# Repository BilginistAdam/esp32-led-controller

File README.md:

<p align="center">
  <picture>
    <source media="(prefers-color-scheme: dark)" srcset="docs/logo/banner-dark.svg">
    
  </picture>
</p>

# LED Controller — ESP32-C3 LED Şerit Kontrolcüsü

12–24 V LED şeritleri WiFi üzerinden açıp kapatan ve PWM ile dimleyen küçük bir kontrol kartı. Proje KiCad donanım dosyalarını, iki firmware seçeneğini (ESPHome / PlatformIO) ve 3D yazıcıyla basılabilen bir kutuyu içerir.

| PCB üst | Şematik |
|---|---|
|  |  |

## Özellikler

- **Kontrol:** ESP32-C3-WROOM-02 (WiFi + BLE). Programlama dahili USB üzerinden USB-C ile yapılıyor, ayrı bir USB-UART çipi yok.
- **Giriş:** 12–24 V DC. PTC sigorta ve TVS ile korunuyor. AP63203 buck regülatör 3.3 V üretiyor.
- **Besleme:** D1/D2 diyotlarıyla kart adaptörden **ya da** sadece USB'den beslenebiliyor, yani programlarken adaptör gerekmiyor.
- **LED sürme:** LED şeridini low-side AO3400A MOSFET anahtarlıyor. 20 kHz PWM kullanılıyor, böylece duyulabilir vızıltı olmuyor. Gate'teki pull-down sayesinde LED boot sırasında kapalı kalıyor.
- **Arayüz:** RESET butonu, BOOT/kullanıcı butonu ve durum LED'i var.
- **Kart:** 64 × 38 mm, 2 katman, 4 × M3 montaj deliği.

## Klasör yapısı

```
hardware/          KiCad projesi (şematik, PCB, proje sembol kütüphanesi)
  BOM.md / BOM.csv malzeme listesi (okunabilir tablo / üretici formatı)
  ledctl-gerbers.zip   üreticiye (JLCPCB/PCBWay vb.) doğrudan yüklenebilir
  fabrication/     Gerber, drill, pick-and-place (pos) dosyaları
  scripts/         şematik/PCB'yi üreten Python betikleri (design.py = tek kaynak)
firmware/
  esphome/         Home Assistant için ESPHome konfigürasyonu
  platformio/      bağımsız Arduino firmware'i (web arayüzü + REST API)
    prebuilt/      derlenmiş factory imajı (0x0 adresine yazılır)
enclosure/         OpenSCAD kaynak + basılmaya hazır STL'ler
docs/              şematik PDF, PCB montaj PDF'i, görseller
  logo/            Bilginier logosu (SVG) + üretici betik (PCB, kutu ve banner aynı kaynaktan)
```

## Malzeme listesi (BOM)

Ayrıntılı liste için [`hardware/BOM.md`](hardware/BOM.md), makineli montaj için [`hardware/BOM.csv`](hardware/BOM.csv) dosyasına bak.

| Adet | Ref | Parça | LCSC |
|---:|---|---|---|
| 1 | U2 | ESP32-C3-WROOM-02-N4 | C2934560 |
| 1 | U1 | AP63203WU-7 (3.3 V buck) | C780769 |
| 1 | Q1 | AO3400A | C20917 |
| 1 | L1 | FNR4030S4R7MT, 4.7 µH | C167874 |
| 1 / 1 / 1 | D1 / D2 / D3 | SS34 / SS14 / SMAJ28A | C8678 / C2480 / C353458 |
| 1 | D4 | Yeşil LED 0603 | C72043 |
| 1 | F1 | PTC 1812 (bkz. BOM.md notu) | — |
| 1 | C1 | 10 µF 50 V 1206 | C13585 |
| 3 | C2, C3, C7 | 100 nF 50 V 0603 | C14663 |
| 2 | C4, C5 | 22 µF 25 V 0805 | C45783 |
| 1 / 1 | C6 / C8 | 10 µF 0805 / 1 µF 0603 | C15850 / C15849 |
| 4 | R1–R4 | 10 kΩ 0603 | C25804 |
| 1 / 1 / 1 | R5 / R6 / R7 | 100 Ω / 100 kΩ / 1 kΩ 0603 | C22775 / C25803 / C21190 |
| 2 | R8, R9 | 5.1 kΩ 0603 | C23186 |
| 2 | J1, J2 | Phoenix 1715721, 2P 5.08 mm | C480516 |
| 1 | J3 | USB-C HRO TYPE-C-31-M-12 | C165948 |
| 1 | J4 | 1×4 pin header (opsiyonel) | C2337 |
| 2 | SW1, SW2 | TS-1187A-B-A-B | C318884 |
| 4 | — | M3 × 20 vida (kutu) | — |

JLCPCB montaj için hazır dosyalar: `hardware/fabrication/ledctl-bom-jlcpcb.csv` ve `ledctl-cpl-jlcpcb.csv`.

## Pin haritası

| GPIO | İşlev |
|---|---|
| IO4 | LED PWM → R5 → Q1 gate |
| IO9 | BOOT / kullanıcı butonu (aktif düşük) |
| IO10 | Durum LED'i (aktif yüksek) |
| IO18 / IO19 | USB D− / D+ (USB-C) |
| IO20 / IO21 | UART RX / TX (J4, opsiyonel) |

## Firmware

### Seçenek A: ESPHome (Home Assistant)

```bash
cd firmware/esphome
cp secrets.yaml.example secrets.yaml   # WiFi bilgilerini gir
esphome run ledctl.yaml                # ilk yükleme USB-C üzerinden
```

Bu seçenek Home Assistant'a "LED Serit" adlı, dimlenebilir bir ışık olarak eklenir. Butona basınca LED açılıp kapanır, durum LED'i WiFi bağlantısını gösterir.

### Seçenek B: PlatformIO (bağımsız)

```bash
cd firmware/platformio
pio run -t upload        # USB-C
pio device monitor
```

1. **WiFi kurulumu:** İlk açılışta kart `LedCtrl-Setup` adında bir WiFi ağı açar. Bu ağa bağlanıp açılan sayfadan kendi WiFi bilgilerini gir.
2. **Web arayüzü:** Kurulumdan sonra `http://led-ctrl.local` adresinden aç/kapat ve parlaklık ayarı yapılabilir.
3. **REST API:**
   ```bash
   curl http://led-ctrl.local/api/state
   curl -X POST http://led-ctrl.local/api/state -d '{"on":true,"brightness":60}'
   curl -X POST http://led-ctrl.local/api/toggle
   ```
4. **Buton:**
   - Kısa basış: aç/kapat
   - Basılı tutma: parlaklığı 100 → 75 → 50 → 25 → 10 sırasıyla değiştirir
   - 8 saniye basılı tutma: WiFi ayarlarını siler
5. **Durum LED'i:**
   - Sürekli yanık: bağlı
   - Yavaş yanıp sönme: bağlanıyor
   - Hızlı yanıp sönme: kurulum modunda
6. **Diğer:** Son durum NVS'e kaydedilir, elektrik kesilip gelince geri yüklenir. Ayrıca OTA güncelleme (ArduinoOTA) destekleniyor.

Hazır imajı yazmak için:

```bash
esptool.py --chip esp32c3 write_flash 0x0 firmware/platformio/prebuilt/ledctl-factory.bin
```

> **Yükleme başlamazsa:** **BOOT**'a basılı tutarken **RESET**'e bas ve bırak. Kart indirme moduna geçer. Normalde USB üzerinden otomatik reset yeterli olur.

## Kutu (3D baskı)

| Parça | Dosya | Baskı yönü |
|---|---|---|
| Gövde | `enclosure/ledctl_case_base.stl` | taban aşağıda |
| Kapak | `enclosure/ledctl_case_lid.stl` | yüzü aşağıda (dosya zaten bu yönde) |

- **Önerilen baskı ayarları:** PETG veya PLA, 0.2 mm katman, %20–30 doluluk. Destek gerekmiyor.
- **Montaj:** 4 adet **M3 × 20** vida kapaktan girer, PCB'yi sıkıştırır ve gövdedeki direklere tutunur. Vidalar plastiğe kendi yolunu açabilir; isteğe bağlı olarak `pilot_d = 4.0` ile heat-set insert de kullanılabilir.
- **Duvara montaj:** Tabanda 20 mm aralıklı iki anahtar deliği var, en fazla 8 mm başlı vida uygun. USB-C aşağı bakacak şekilde asılır.
- **Bantla montaj:** Taban tamamen düz olduğu için çift taraflı bantla da yapıştırılabilir.
- **Butonlar:** RESET ve BOOT butonları kapaktaki esnek dillerle basılır. Durum LED'inin ışığı kapaktaki tüpten görünür.
- **Terminaller:** Vidalarına kapaktaki deliklerden tornavidayla erişilir.
- **Ölçüler:** `enclosure/ledctl_case.scad` içindeki parametrelerden (tolerans, duvar kalınlığı, yükseklik) değiştirilebilir.

```bash
openscad -D 'part="base"' -o enclosure/ledctl_case_base.stl enclosure/ledctl_case.scad
openscad -D 'part="lid"'  -o enclosure/ledctl_case_lid.stl  enclosure/ledctl_case.scad
```

## Üretim

1. `hardware/ledctl-gerbers.zip` dosyasını PCB üreticisine yükle. Ayarlar: 2 katman, 1.6 mm, 1 oz bakır.
2. Montaj için `hardware/BOM.csv` (okunabilir hali: `hardware/BOM.md`) ve `hardware/fabrication/ledctl-pos.csv` dosyalarını kullan.
3. ESP modülünün anteni kartın sağ kenarından yaklaşık 6 mm dışarı taşar. Bu bilinçli bir tercih: antenin altında bakır olmaması gerekiyor. Kutu bu taşmaya göre tasarlandı.

## Tasarım notları ve sınırlar

- **Akım:** AO3400A ile kart yaklaşık **3 A** LED akımı için uygun. 24 V'ta bu yaklaşık 70 W, 12 V'ta yaklaşık 36 W eder. Daha yüksek akım için daha güçlü bir MOSFET kullanılmalı ve LED izleri genişletilmeli.
- **Gerilim:** AP63203 en fazla 32 V girişe dayanır. 24 V adaptörlerde sorun yok. TVS (SMAJ28A) kısa süreli darbelere karşı korur, ama sürekli aşırı gerilimden korumaz.
- **F1 sigorta:** 3 A / 24 V için 1812 kılıfta uygun bir PTC yok. Seçenekler [`hardware/BOM.md`](hardware/BOM.md) notunda anlatılıyor.
- **Routing:** İzler Freerouting ile otomatik çizildi. DRC'de elektriksel hata yok, sadece kozmetik silkscreen uyarıları var. Sipariş vermeden önce KiCad 8/9'da ERC ve DRC'yi kendin de çalıştır.
- **Yeniden üretme:** `hardware/scripts/` içindeki betikler şematik ve PCB'yi `design.py` ve `placement.py` dosyalarından üretir. Logo ve isim en son `add_branding.py` ile silkscreen'e eklenir. Bunun için KiCad 7+ Python (`pcbnew`) ve otomatik routing için Freerouting gerekir (`FREEROUTING_JAR` ortam değişkeni).

## Lisans

[MIT](LICENSE). Donanım dosyaları, firmware ve kutu dahil projenin tamamı bu lisansla yayınlanır.

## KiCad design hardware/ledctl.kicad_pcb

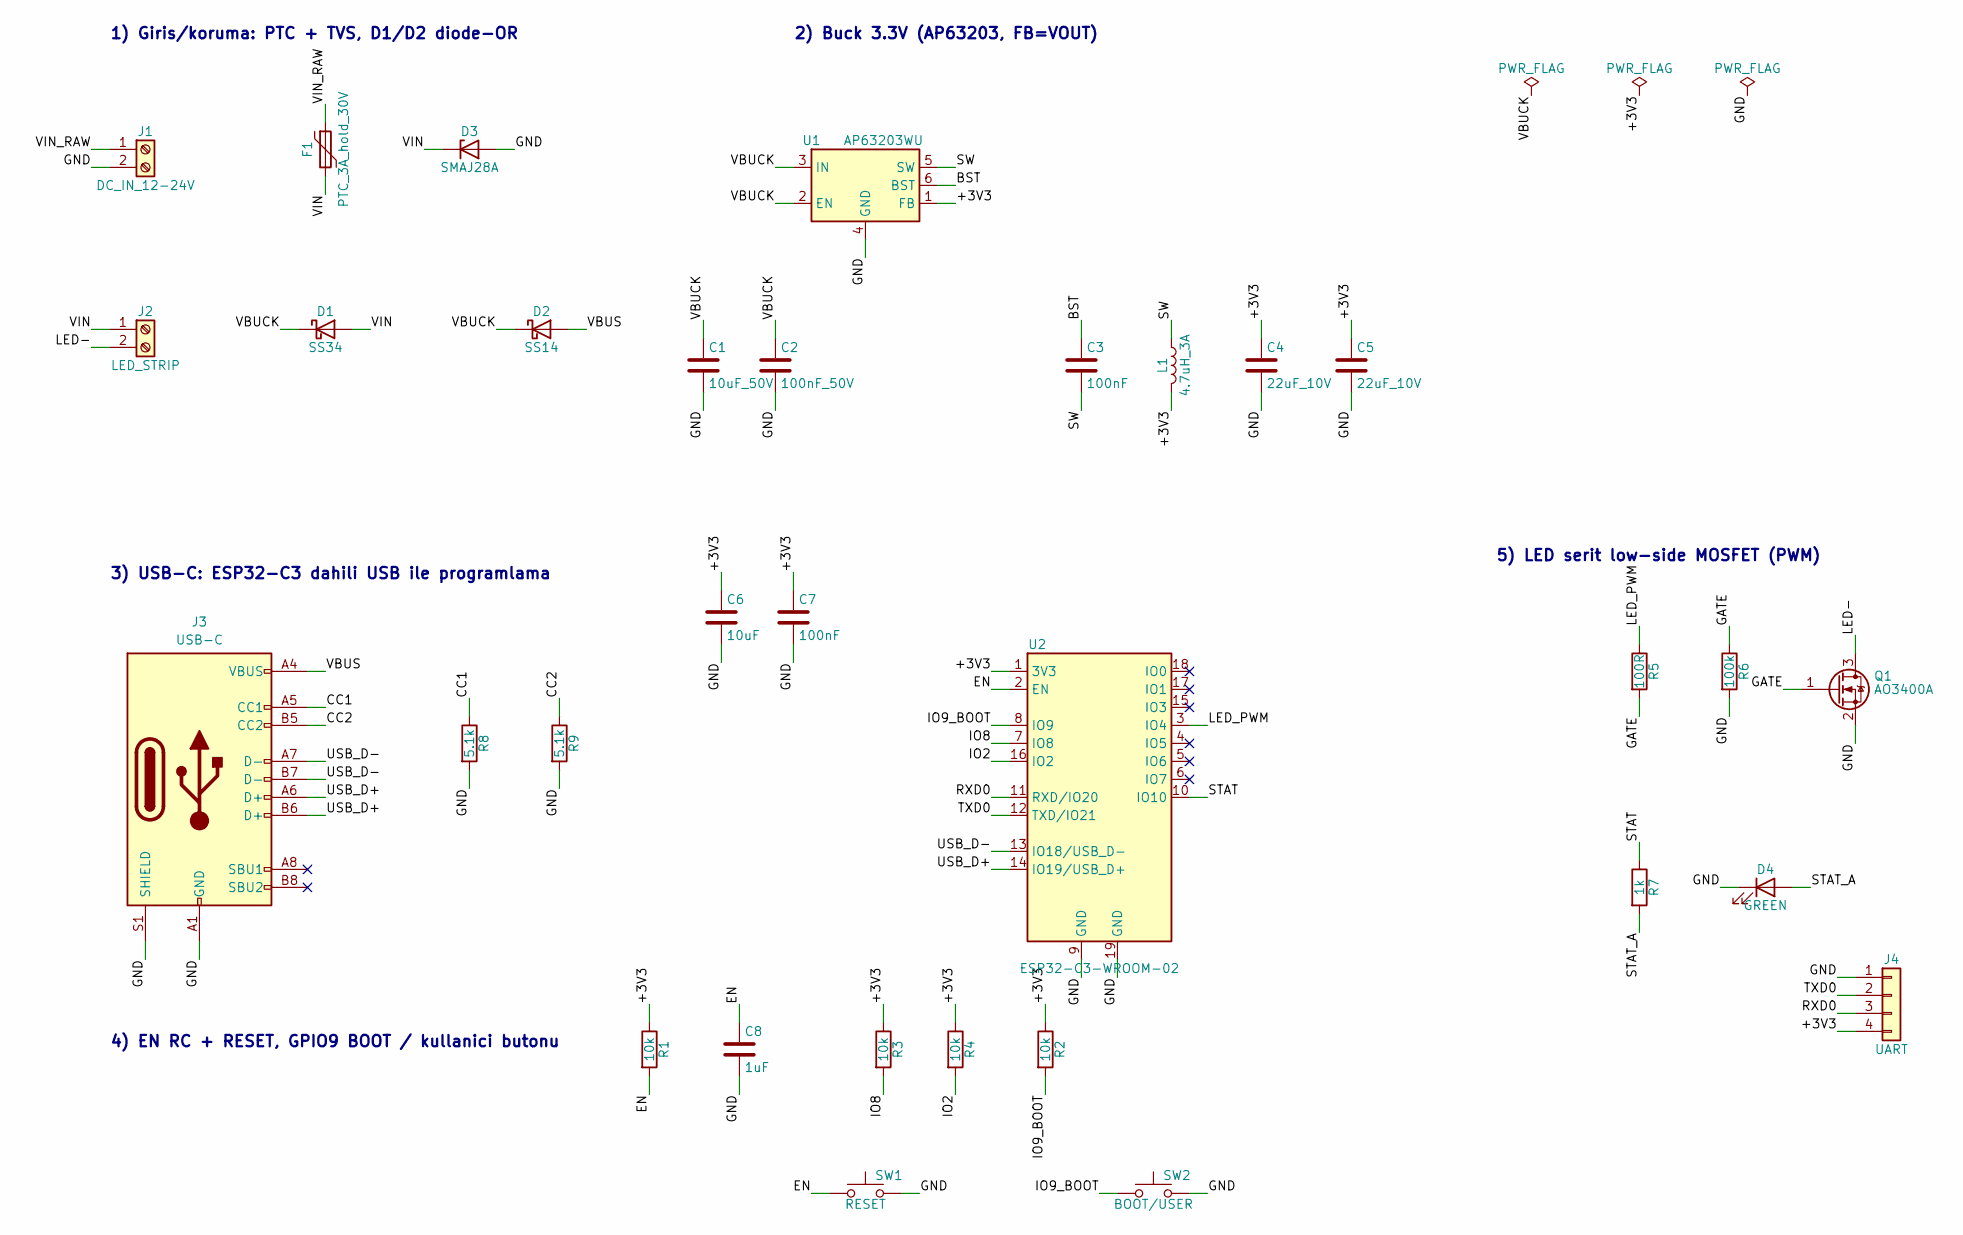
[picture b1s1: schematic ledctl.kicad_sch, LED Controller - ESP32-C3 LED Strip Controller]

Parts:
C1: 10uF_50V; C_1206_3216Metric
C2: 100nF_50V; C_0603_1608Metric
C3, C7: 100nF; C_0603_1608Metric
C4, C5: 22uF_10V; C_0805_2012Metric
C6: 10uF; C_0805_2012Metric
C8: 1uF; C_0603_1608Metric
D1: SS34; D_SMA
D2: SS14; D_SMA
D3: SMAJ28A; D_SMA
D4: GREEN; LED_0603_1608Metric
F1: PTC_3A_hold_30V; Fuse_1812_4532Metric
J1: DC_IN_12-24V; TerminalBlock_Phoenix_MKDS-1,5-2-5.08_1x02_P5.08mm_Horizont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
J2: LED_STRIP; TerminalBlock_Phoenix_MKDS-1,5-2-5.08_1x02_P5.08mm_Horizont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
J3: USB-C; USB_C_Receptacle_HRO_TYPE-C-31-M-12
J4: UART; PinHeader_1x04_P2.54mm_Vertical
L1: 4.7uH_3A; L_Changjiang_FNR4030S
Q1: AO3400A; SOT-23
R1, R2, R3, R4: 10k; R_0603_1608Metric
R5: 100R; R_0603_1608Metric
R6: 100k; R_0603_1608Metric
R7: 1k; R_0603_1608Metric
R8, R9: 5.1k; R_0603_1608Metric
SW1: RESET; SW_Push_1P1T_XKB_TS-1187A
SW2: BOOT/USER; SW_Push_1P1T_XKB_TS-1187A
U1: AP63203WU; TSOT-23-6
U2: ESP32-C3-WROOM-02

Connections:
+3V3: C4.1, C5.1, C6.1, C7.1, J4.4, L1.2, R1.1, R2.1, R3.1, R4.1, U1.1 (FB), U2.1 (3V3)
BST: C3.1, U1.6 (BST)
CC1: J3.A5 (CC1), R8.1
CC2: J3.B5 (CC2), R9.1
EN: C8.1, R1.2, SW1.1, U2.2 (EN)
GATE: Q1.1 (G), R5.2, R6.1
GND: C1.2, C2.2, C4.2, C5.2, C6.2, C7.2, C8.2, D3.2 (A), D4.1 (K), J1.2, J3.A1 (GND), J3.A12 (GND), J3.B1 (GND), J3.B12 (GND), J3.S1 (SHIELD), J4.1, Q1.2 (S), R6.2, R8.2, R9.2, SW1.2, SW2.2, U1.4 (GND), U2.9 (GND), U2.19 (GND)
IO2: R4.2, U2.16 (IO2)
IO8: R3.2, U2.7 (IO8)
IO9_BOOT: R2.2, SW2.1, U2.8 (IO9)
LED-: J2.2, Q1.3 (D)
LED_PWM: R5.1, U2.3 (IO4)
RXD0: J4.3, U2.11 (RXD/IO20)
STAT: R7.1, U2.10 (IO10)
STAT_A: D4.2 (A), R7.2
SW: C3.2, L1.1, U1.5 (SW)
TXD0: J4.2, U2.12 (TXD/IO21)
USB_D+: J3.A6 (D+), J3.B6 (D+), U2.14 (IO19/USB_D+)
USB_D-: J3.A7 (D-), J3.B7 (D-), U2.13 (IO18/USB_D-)
VBUCK: C1.1, C2.1, D1.1 (K), D2.1 (K), U1.2 (EN), U1.3 (IN)
VBUS: D2.2 (A), J3.A4 (VBUS), J3.A9 (VBUS), J3.B4 (VBUS), J3.B9 (VBUS)
VIN: D1.2 (A), D3.1 (K), F1.2, J2.1
VIN_RAW: F1.1, J1.1

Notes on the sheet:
1) Giris/koruma: PTC + TVS, D1/D2 diode-OR
2) Buck 3.3V (AP63203, FB=VOUT)
3) USB-C: ESP32-C3 dahili USB ile programlama
4) EN RC + RESET, GPIO9 BOOT / kullanici butonu
5) LED serit low-side MOSFET (PWM)

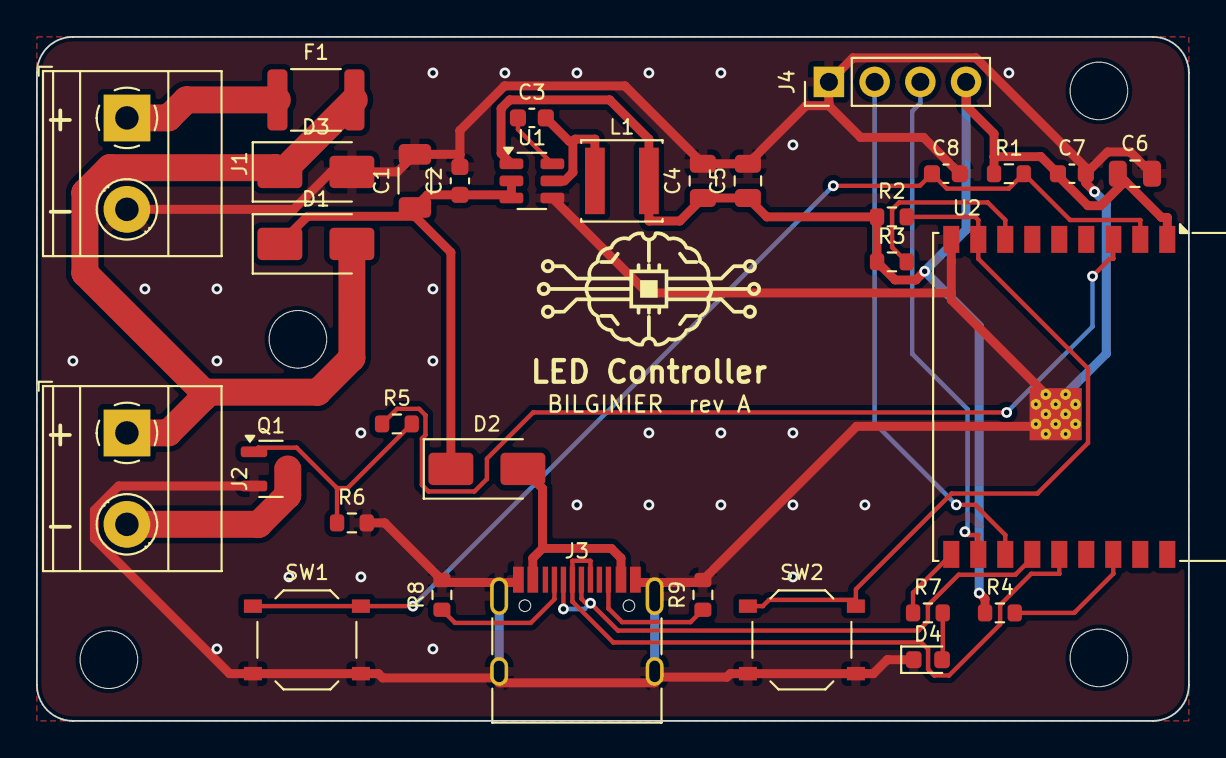
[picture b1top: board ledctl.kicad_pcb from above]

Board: 2 copper layers, 64.0 x 38.0 mm, 36 parts (0 on the bottom side), 23 nets.

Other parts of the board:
H1, H2, H3, H4: MountingHole_3.2mm_M3

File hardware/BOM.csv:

Qty,References,Value,Description,Package / Footprint,Manufacturer part number,LCSC
1,U2,ESP32-C3-WROOM-02-N4,"Wi-Fi/BLE module, 4 MB flash, PCB antenna",ESP32-C3-WROOM-02,Espressif ESP32-C3-WROOM-02-N4,C2934560
1,U1,AP63203WU,"Synchronous buck 3.8-32 V in, 3.3 V / 2 A out, 1.1 MHz",TSOT-23-6,Diodes Inc. AP63203WU-7,C780769
1,Q1,AO3400A,"N-MOSFET 30 V / 5.7 A, logic level (LED strip switch)",SOT-23,Alpha & Omega AO3400A,C20917
1,L1,4.7uH,"Power inductor 4.7 uH, Isat 3.2 A, shielded",4.0 x 4.0 mm (FNR4030S),Changjiang FNR4030S4R7MT,C167874
1,D1,SS34,"Schottky 40 V / 3 A (adapter -> buck, diode-OR)",SMA,MDD SS34,C8678
1,D2,SS14,"Schottky 40 V / 1 A (USB VBUS -> buck, diode-OR)",SMA,MDD SS14,C2480
1,D3,SMAJ28A,"TVS 28 V standoff, unidirectional",SMA,Jingdao SMAJ28A,C353458
1,D4,GREEN,"Status LED, green",0603,Everlight 19-217/GHC-YR1S2/3T,C72043
1,F1,PTC,"Resettable fuse - see BOM.md note: no 1812 part covers 3 A at 24 V",1812,TBD,
1,C1,10uF 50V,"Buck input bulk, X5R",1206,Samsung CL31A106KBHNNNE,C13585
3,C2 C3 C7,100nF 50V,"Buck input HF (C2), bootstrap (C3), module decoupling (C7), X7R",0603,Yageo CC0603KRX7R9BB104,C14663
2,C4 C5,22uF 25V,"Buck output, X5R",0805,Samsung CL21A226MAQNNNE,C45783
1,C6,10uF 25V,"Module bulk decoupling, X5R",0805,Samsung CL21A106KAYNNNE,C15850
1,C8,1uF 50V,"EN RC delay, X5R",0603,Samsung CL10A105KB8NNNC,C15849
4,R1 R2 R3 R4,10k 1%,"EN pull-up, strapping pull-ups (IO9 / IO8 / IO2)",0603,UNI-ROYAL 0603WAF1002T5E,C25804
1,R5,100R 1%,"MOSFET gate series resistor",0603,UNI-ROYAL 0603WAF1000T5E,C22775
1,R6,100k 1%,"MOSFET gate pull-down (LED off during boot)",0603,UNI-ROYAL 0603WAF1003T5E,C25803
1,R7,1k 1%,"Status LED series resistor",0603,UNI-ROYAL 0603WAF1001T5E,C21190
2,R8 R9,5.1k 1%,"USB-C CC1/CC2 pull-downs (sink role)",0603,UNI-ROYAL 0603WAF5101T5E,C23186
2,SW1 SW2,TS-1187A,"Tactile switch 5.1 x 5.1 x 1.5 mm (RESET / BOOT-user)",SMD 4-pad,XKB TS-1187A-B-A-B,C318884
1,J3,USB-C 16P,"USB 2.0 Type-C receptacle, SMD + THT shell",HRO TYPE-C-31-M-12,Korean Hroparts TYPE-C-31-M-12,C165948
2,J1 J2,2-pos 5.08 mm,"Screw terminal block (J1 = 12-24 V in, J2 = LED strip)",Phoenix MKDS 1.5/2-5.08,Phoenix Contact 1715721,C480516
1,J4,1x4 2.54 mm,"UART/debug header (optional; cut from 1x40 strip)",PinHeader_1x04_P2.54mm,BOOMELE 2.54-1*40P,C2337
,,,,,,
,,,Enclosure hardware,,,
4,,M3 x 20,"Pan head self-tapping (or machine screw with M3 heat-set inserts)",,,
